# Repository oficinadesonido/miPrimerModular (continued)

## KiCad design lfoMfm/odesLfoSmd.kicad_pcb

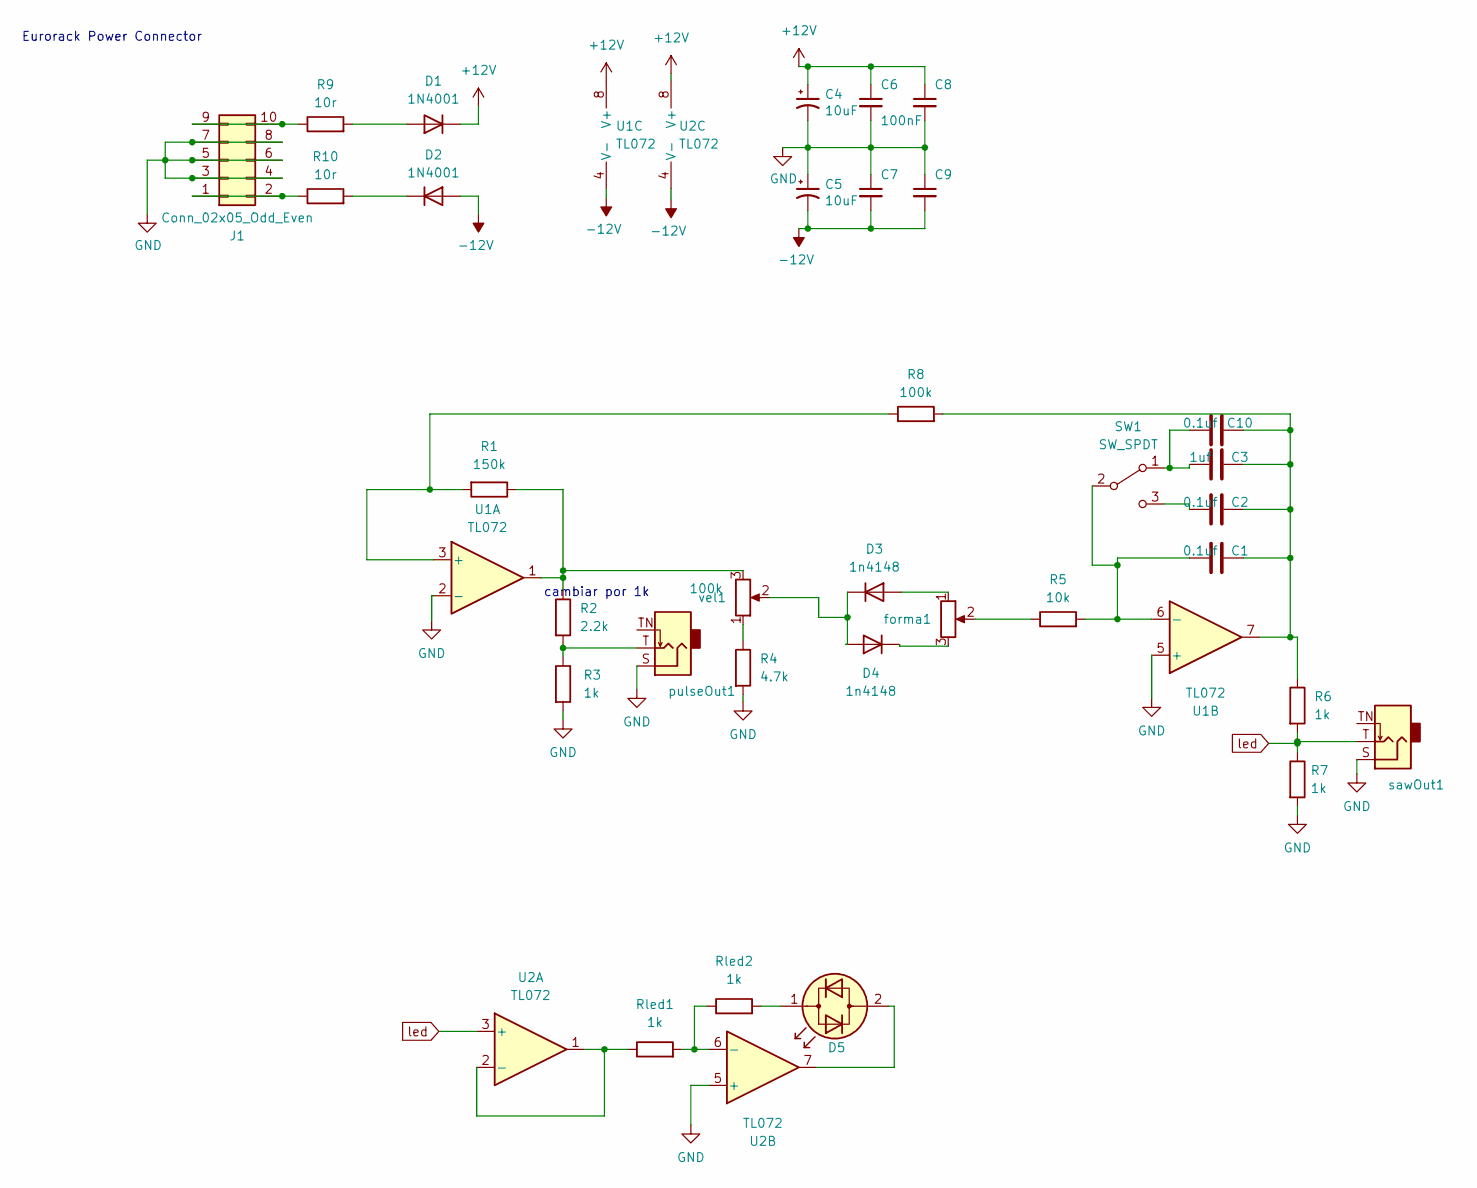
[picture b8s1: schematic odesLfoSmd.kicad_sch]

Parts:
C1, C2: 0.1uf; C_0603_1608Metric_Pad1.08x0.95mm_HandSolder
C3: 1uf; C_0603_1608Metric_Pad1.08x0.95mm_HandSolder
C4, C5: 10uF; C_0805_2012Metric_Pad1.18x1.45mm_HandSolder
C6, C7, C8, C9: 100nF; C_0603_1608Metric_Pad1.08x0.95mm_HandSolder
C10: 0.1uf; C_Disc_D4.3mm_W1.9mm_P5.00mm
D1, D2: 1N4001; D_SOD-123
D3, D4: 1n4148; D_SOD-123
D5: LED_Dual_Bidirectional; LED_D3.0mm_Clear
J1: Conn_02x05_Odd_Even; IDC-Header_2x05_P2.54mm_Vertical
R1: 150k; R_0603_1608Metric_Pad0.98x0.95mm_HandSolder
R2: 2.2k; R_0603_1608Metric_Pad0.98x0.95mm_HandSolder
R3, R6, R7: 1k; R_0603_1608Metric_Pad0.98x0.95mm_HandSolder
R4: 4.7k; R_0603_1608Metric_Pad0.98x0.95mm_HandSolder
R5: 10k; R_0603_1608Metric_Pad0.98x0.95mm_HandSolder
R8: 100k; R_0603_1608Metric_Pad0.98x0.95mm_HandSolder
R9, R10: 10r; R_0603_1608Metric_Pad0.98x0.95mm_HandSolder
Rled1, Rled2: 1k; R_0603_1608Metric_Pad0.98x0.95mm_HandSolder
SW1: SW_SPDT; colader
U1, U2: TL072; SOP-8_3.76x4.96mm_P1.27mm
forma1: 500k; PotGndPin1
pulseOut1: AudioJack2_SwitchT; jackEuroTSTN
sawOut1: AudioJack2_SwitchT; jackEuroTSTN
vel1: 100k; PotGndPin1

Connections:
+12V: C4.1, C6.1, C8.1, D1.1 (K), U1.8 (V+), U2.8 (V+)
-12V: C5.2, C7.2, C9.2, D2.2 (A), U1.4 (V-), U2.4 (V-)
GND: C4.2, C5.1, C6.2, C7.1, C8.2, C9.1, J1.3, J1.4, J1.5, J1.6, J1.7, J1.8, R3.2, R4.2, R7.2, U1.2 (-), U1.5 (+), U2.5 (+), pulseOut1.S, sawOut1.S
unnamed: C1.2, C2.2, C3.2, C10.2, R6.1, R8.2, U1.7
unnamed: D1.2 (A), R9.2
unnamed: D2.1 (K), R10.2
unnamed: D3.2 (A), forma1.1
unnamed: D3.1 (K), D4.2 (A), vel1.2
unnamed: D4.1 (K), forma1.3
unnamed: D5.2 (AK), U2.7
unnamed: D5.1 (KA), Rled2.2
unnamed: J1.1, J1.2, R10.1
unnamed: J1.9, J1.10, R9.1
unnamed: R1.1, R2.1, U1.1, vel1.3
unnamed: R2.2, R3.1, pulseOut1.T
unnamed: R4.1, vel1.1
unnamed: R5.1, forma1.2
unnamed: C3.1, C10.1, SW1.1 (A)
unnamed: C1.1, R5.2, SW1.2 (B), U1.6 (-)
unnamed: C2.1, SW1.3 (C)
unnamed: R1.2, R8.1, U1.3 (+)
unnamed: Rled1.1, U2.1, U2.2 (-)
unnamed: Rled1.2, Rled2.1, U2.6 (-)
led: R6.2, R7.1, U2.3 (+), sawOut1.T

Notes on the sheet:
cambiar por 1k
Eurorack Power Connector

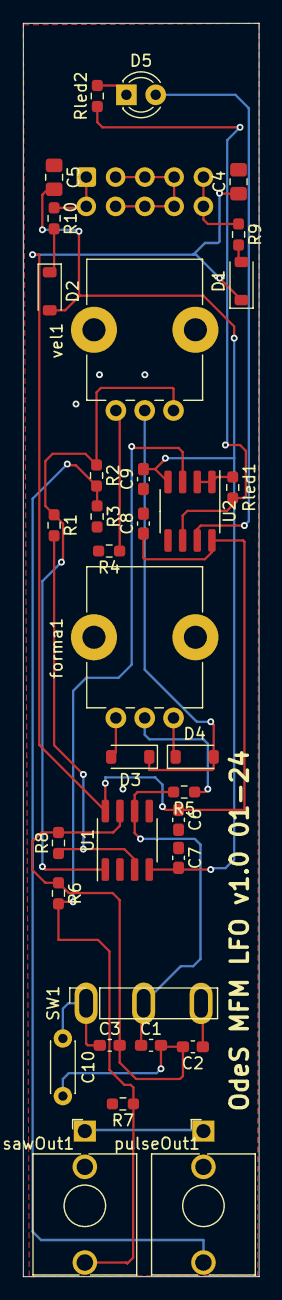
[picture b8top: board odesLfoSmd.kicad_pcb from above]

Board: 2 copper layers, 20.4 x 108.7 mm, 35 parts (1 on the bottom side), 24 nets.

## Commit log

2024-07-27 Update README.md
    inicio
2024-08-08 Folder Name change
    cambio de nombres en carpetas
2024-08-08 new folder vcfont
2024-08-08 change
2025-09-05 Rename acordesMidi_12.ino to VCO Chords.ino
2025-09-05 Rename VCO Chords.ino to VCO Chords.ino
